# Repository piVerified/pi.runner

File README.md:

# pi.runner

pi.runner is a BLE IoT device, that turns my noemal 'dumb' treadmill into a smart treadmil that connects to google health and reads the distance covered and my pase accurately 

##### This device directly integrates into my old treadmil through handwitring, it will draw power forom the treadmil console's 2x AA batteris, which voltage is steppded up via voltage booster, also the inbuild reed switch magnetic sensor of the tradmill will be hoked directly to my custom made pcb.
---
# Features

1. Tap-to-Wake
2. NFC Mode Trigger
4. Real-Time Speed Tracking
5. Precision Distance Logging
6. Automatic Workout Saving
7. Smart Home Integration

## Fusion 360

### Case

| Top | Side |
| :--: | :--: |
| *(coming soon)* | *(coming soon)* |

---
## KiCAD

| Schematic | PCB |
| :-------: | :-: |
|  |  |

---
Adittion to pcb two more module will be needed to be connected to the pcb but will be handwired as i could not find any symbol of footprint for them 
| CKT Diagram |  
| :--: | 
| *(coming soon)* | 

---
# Softwares Used

* KiCAD -> PCB Design
* Fusion 360 -> Case design
* MicroPython / Arduino IDE -> Firmware

---
# Bibliography

> This project would not have been possible without the help of the amazing people of the internet, the Hack Club blueprint guide, and a bit of AI.

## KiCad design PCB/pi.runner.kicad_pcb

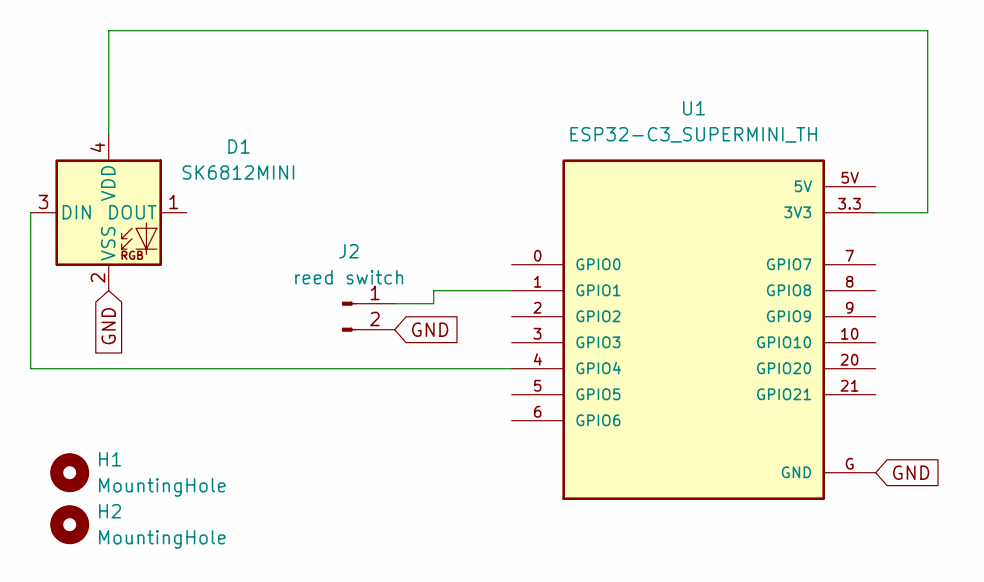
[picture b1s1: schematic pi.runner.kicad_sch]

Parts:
D1: SK6812MINI; LED_SK6812MINI_PLCC4_3.5x3.5mm_P1.75mm
H1, H2: MountingHole; MountingHole_3.2mm_M3
J2: reed switch; C_Rect_L7.2mm_W3.5mm_P5.00mm
U1: ESP32-C3_SUPERMINI_TH; MODULE_ESP32-C3_SUPERMINI_TH

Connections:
GND: D1.2 (VSS), J2.2, U1.G (GND)
unnamed: D1.3 (DIN), U1.4 (GPIO4)
unnamed: D1.4 (VDD), U1.3.3 (3V3)
unnamed: J2.1, U1.1 (GPIO1)

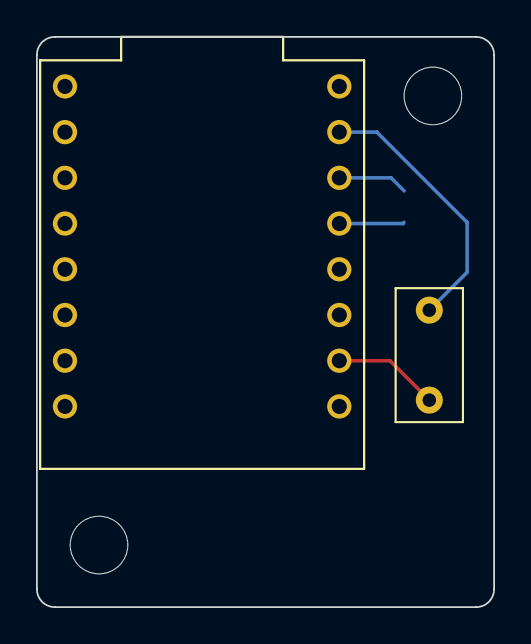
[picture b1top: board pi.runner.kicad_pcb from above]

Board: 2 copper layers, 25.4 x 31.7 mm, 5 parts (1 on the bottom side), 4 nets.

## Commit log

2026-03-01 update Features
    Updated project name and description to reflect new IoT device functionality.
2026-03-02 updated BOM
2026-03-02 completed firmware
